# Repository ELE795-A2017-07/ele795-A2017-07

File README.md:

This is the project as handed out by the previous team. It used a Arduino node rather than a Raspberry Pi one.

# This is the BELIOT project
This is an Internet Of Things project.
This project contains an Arduino Nano which is the core microcontroller of module.
The module contains an RF circuit (inAir9B) with LoRaWAN technology. This node sends
data to a Raspberry Pi via RF and the Raspberry Pi posts its data to a Webserver via a Ruby script.
Webserver (Ruby on Rails app) can be reached at beliotv3.herokuapp.com. Data is stored into InfluxDB and can be visualized with Grafana.

This unit monitors:
- soil humidity and temperature
- air humidity and temperature
- Ozone concentration
- Dust concentration
- GPS
- Battery Life

Here is a picture of the Arduino node:

Here is the circuitry inside the Stevenson Cage:

Here is the Raspberry Pi Gateway to receive/send data:

Here is a picture of a successful transmission from the Arduino node to the Raspberry Pi (seen on rasp console):

Here is the landing page of the website:

Here is some data plotted using Grafana:

The PCBs and electronics circuits were made using the KiCad software.

A User Manual (in French) is to be found on PDF.

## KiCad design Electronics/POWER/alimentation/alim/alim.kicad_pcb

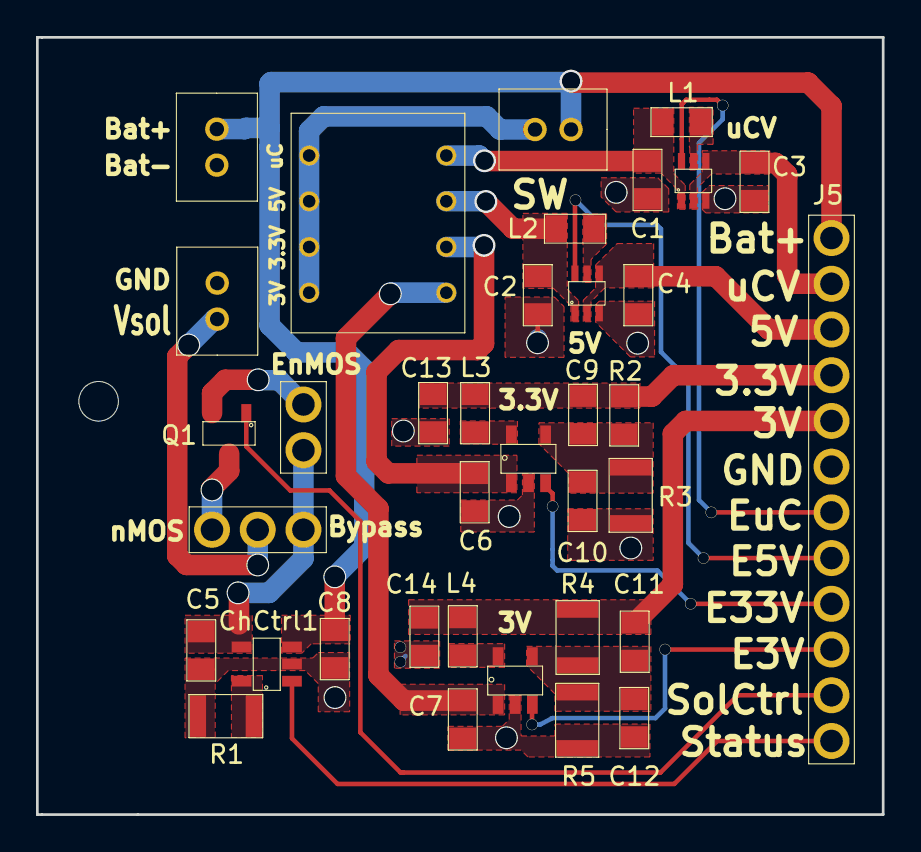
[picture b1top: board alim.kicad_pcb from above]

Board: 2 copper layers, 47.0 x 43.2 mm, 36 parts (0 on the bottom side), 28 nets.

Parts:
C1, C2, C3, C4: 10u; 0805
C5, C6, C7, C8, C13, C14: 4.7u; 0805
C9, C11: 36p; 0805
C10, C12: 180p; 0805
ChCtrl1: ChargeCtrl_MCP73831/2; SOT-23-5_MCP7383X
J1: SolCell; Connect_X2_Power
J2: nMOS_or_Direct; Header_X3_0p1
J3: Bat3.6V; Connect_X2_Power
J4: En_SolCtrl; Header_X2_0p1
J5: AlimConnector; Header_X12_0p1
L1, L2: 4.7u; 0805
L3, L4: 10u; 0805
PB1: PushButton; Connect_X2_Power
Q1: SI2342DS-T1-GE3; SOT-23_SI2342DS
R1: 6.04k; 1210
R2: 510k; 0805
R3, R5: 91k; 1210
R4: 453k; 1210
Reg1, Reg2: StepUpRegulator_TPS61220; SOT-363_TPS61222
Reg3, Reg4: StepDownRegulator_TPS62200; SOT-23-5_TPS6220x
SW1: DipSwitch4; DIP_Switch_X4

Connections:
3.3V: C9.1, C13.1, J5.4, L3.2, R2.1
3V: C11.1, C14.1, J5.5, L4.2, R4.1
5V: C4.1, J5.3, Reg2.2, Reg2.4
Bat+: C8.1, ChCtrl1.3, J3.1, J5.1, PB1.1
Bat-: C1.2, C2.2, C3.2, C4.2, C5.2, C6.2, C7.2, C8.2, C10.2, C12.2, C13.2, C14.2, ChCtrl1.2, J1.2, J3.2, J5.6, R1.2, R3.2, R5.2, Reg1.3, Reg2.3, Reg3.2, Reg4.2
EN3.3V: J5.9, Reg3.3
EN3V: J5.10, Reg4.3
EN5V: J5.8, Reg2.6
ENuC: J5.7, Reg1.6
unnamed: C5.1, ChCtrl1.4, J2.1, J4.2
unnamed: C9.2, C10.1, R2.2, R3.1, Reg3.4
unnamed: C11.2, C12.1, R4.2, R5.1, Reg4.4
unnamed: ChCtrl1.5, R1.1
unnamed: J2.3, Q1.3
unnamed: J4.1, Q1.2
unnamed: L1.1, Reg1.5
unnamed: L2.1, Reg2.5
unnamed: L3.1, Reg3.5
unnamed: L4.1, Reg4.5
SolCtrl: J5.11, Q1.1
Status: ChCtrl1.1, J5.12
Vch3.3V: C6.1, Reg3.1, SW1.6
Vch3V: C7.1, Reg4.1, SW1.5
Vch5V: C2.1, L2.2, Reg2.1, SW1.7
VchuC: C1.1, L1.2, Reg1.1, SW1.8
Von: PB1.2, SW1.1, SW1.2, SW1.3, SW1.4
Vsol: J1.1, J2.2
uCV: C3.1, J5.2, Reg1.2, Reg1.4

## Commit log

2017-09-18 Add initial files
    .gitignore (empty)
    LICENSE.txt (Creative Commons 3.0 BY-NC-ND, as per ÉTS guidelines spelled out here: https://www.etsmtl.ca/Etudiants-actuels/Cycles-sup/.../Guidelines-for-writing.pdf)
    README.md (stub)
2017-09-23 Fix grammar in README.md
2017-09-23 POWER: track files rather than archive
2017-09-23 SENSOR_UNIT: track files rather than archive
2017-09-23 Untrack archive within the archive
    The same content was already part of the primary archive
2017-09-23 POWER: untrack archive within the archive
    Same as previous
2017-09-23 Prepare Lora_Ping_Pong_v1 for actual version control
2017-09-23 Version control LoRa_Ping_Pong (version 2)
2017-09-23 Prepare Dust_sensor_v1 for version control
2017-09-23 Dust sensor v2 (version controlled)
2017-09-23 Prepare Soil_moisture_v1 for version control
2017-09-23 Soil_moisture v2 (version controlled)
2017-09-23 Prepare O3_sensor_v1 for version control
2017-09-23 O3_sensor v2 (version controlled)
2017-09-23 Prepare Soil_temp_v1 for version control
2017-09-23 Soil_temp v2 (version controlled)
2017-09-23 Prepare GPS_v2 for version control
2017-09-23 POWER: Unwrap one layer of directory
2017-09-23 SENSOR_UNIT: unwrap one layer of directory
2017-11-25 Mention that this is the previous version of the project
